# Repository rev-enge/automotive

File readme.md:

# Automotive electronics

Reverse engineered (parts) of electronic equipment from all kinds of
 automotive stuff like cars / diesel engines etc.

Probably most of it are only small reverse engineered parts, pinouts etc.

# Table of contents

* ECM2.1 => [Volvo/ECM2.1](Volvo/ecm2.1/readme.md)

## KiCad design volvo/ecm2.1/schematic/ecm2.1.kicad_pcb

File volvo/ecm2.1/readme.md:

# Identification of the module

Article numer: 60100001 P06

# Description

This unit is an ECM2.1 for a TAD734GE 6 Cylinder 250kW diesel Engine.

# Utilities used to create the drawings

The schematic diagram is made with KiCad 6.0.11

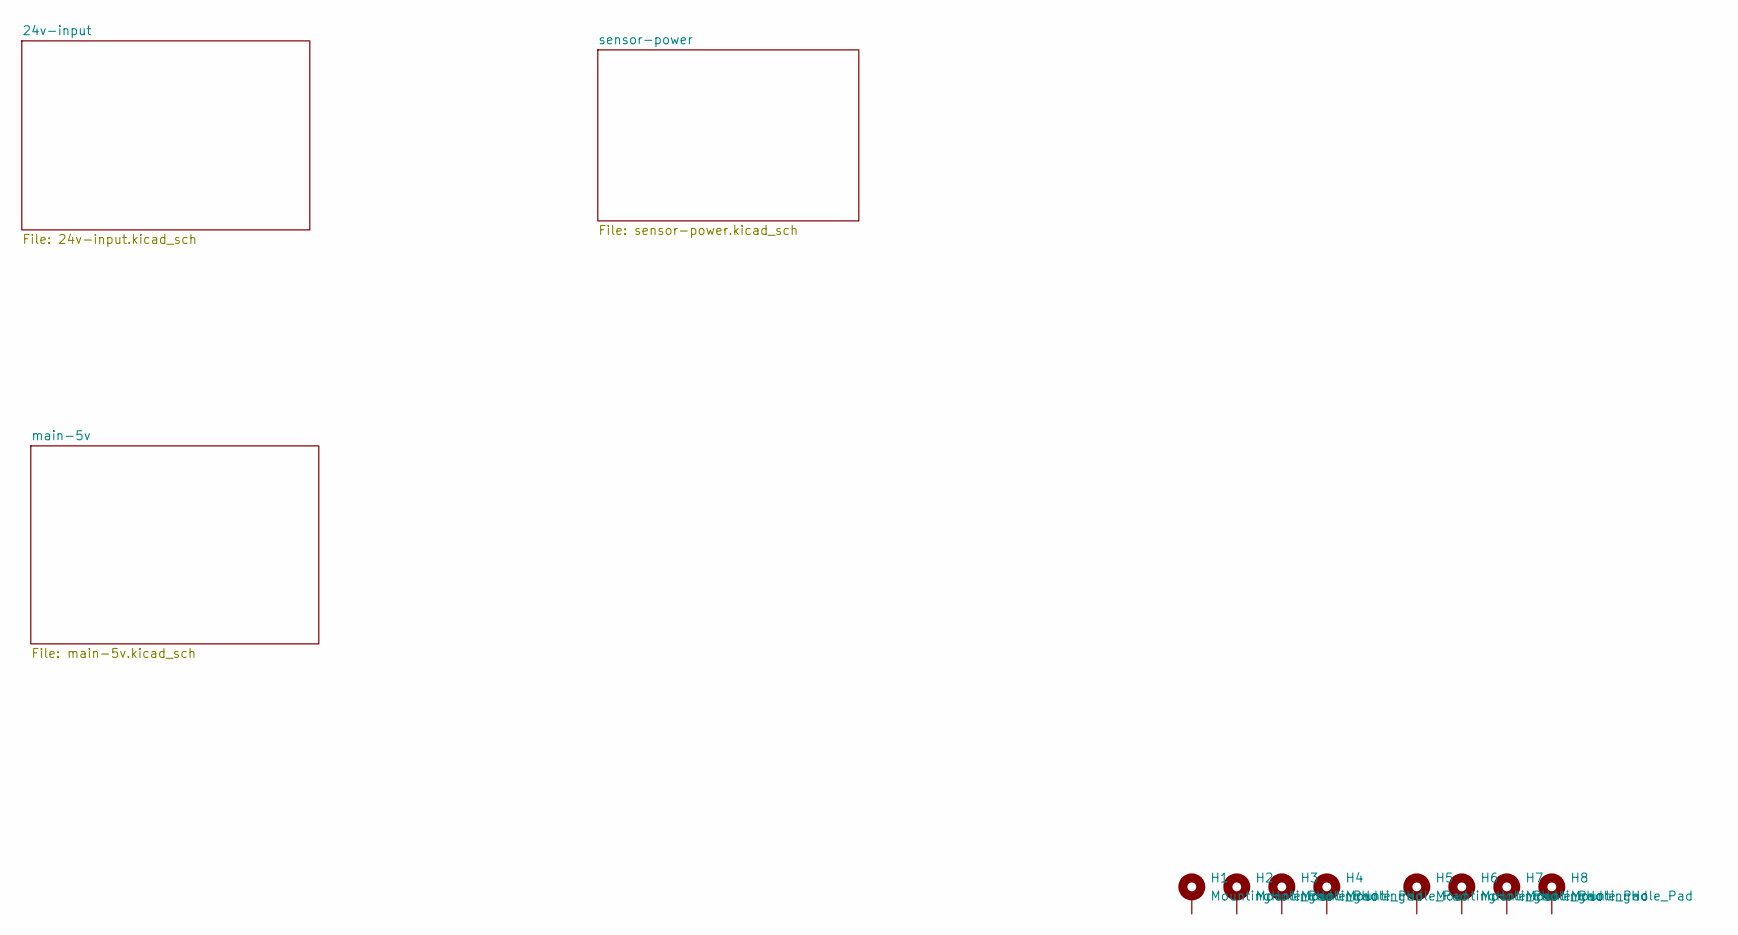
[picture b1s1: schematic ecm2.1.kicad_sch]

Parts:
H1, H2, H3, H4: MountingHole_Pad; MountingHole_5mm_Pad_Via
H5, H6, H7, H8: MountingHole_Pad; MountingHole_5.3mm_M5_DIN965_Pad_TopBottom

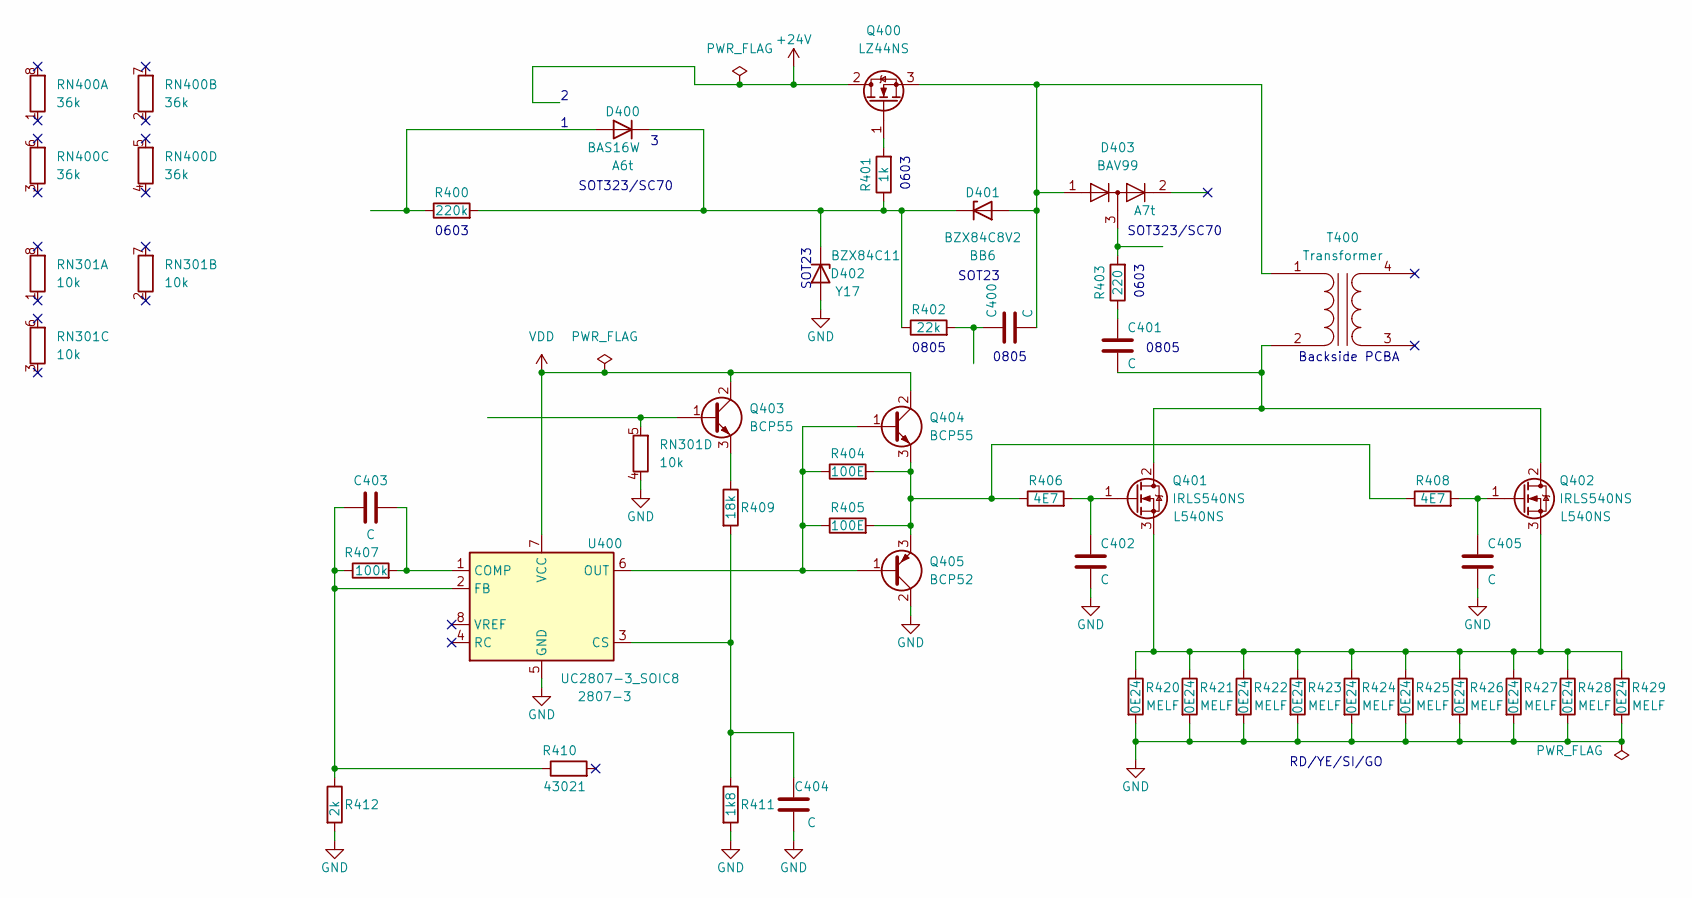
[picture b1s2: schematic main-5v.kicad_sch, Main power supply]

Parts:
C400, C401, C402, C403, C404, C405: C; C_0805_2012Metric
D400: BAS16W; SOT-323_SC-70
D401: BZX84C8V2; SOT-23
D402: BZX84C11; SOT-23
D403: BAV99; SOT-23
Q400: LZ44NS; TO-252-2
Q401, Q402: IRLS540NS; TO-252-3_TabPin2
Q403, Q404: BCP55; SOT-223
Q405: BCP52; SOT-223
R400: 220k; R_0603_1608Metric
R401: 1k; R_0603_1608Metric
R402: 22k; R_0805_2012Metric
R403: 220; R_0603_1608Metric
R404, R405: 100E; R_0805_2012Metric
R406, R408: 4E7; R_0805_2012Metric
R407: 100k; R_0805_2012Metric
R409: 18k; R_0805_2012Metric
R410: 43021; R_0805_2012Metric
R411: 1k8; R_0805_2012Metric
R412: 2k; R_0805_2012Metric
R420, R421, R422, R423, R424, R425, R426, R427, R428, R429: 0E24; R_1206_3216Metric
RN301: 10k; R_Array_Convex_4x0603
RN400: 36k; R_Array_Convex_4x0603
T400: Transformer; Transformer_37x44
U400: UC2807-3_SOIC8; SOIC-8_3.9x4.9mm_P1.27mm

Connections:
+24V: Q400.2 (D)
GND: C402.2, C404.1, C405.2, D402.1 (A), Q405.2 (C), Q405.4 (C), R411.2, R412.2, R420.2, R421.2, R422.2, R423.2, R424.2, R425.2, R426.2, R427.2, R428.2, R429.2, RN301.4 (R4.1), U400.5 (GND)
unnamed: C400.1, R402.2
unnamed: C400.2, D401.1 (A), D403.1 (K), Q400.3 (S), T400.1 (AA)
unnamed: C401.1, R403.1
unnamed: C401.2, Q401.2 (D), Q402.2 (D), T400.2 (AB)
unnamed: C402.1, Q401.1 (G), R406.2
unnamed: C403.1, R407.1, R410.1, R412.1, U400.2 (FB)
unnamed: C403.2, R407.2, U400.1 (COMP)
unnamed: C404.2, R409.2, R411.1, U400.3 (CS)
unnamed: C405.1, Q402.1 (G), R408.2
unnamed: D400.1 (A), R400.1
unnamed: D400.3 (K), D401.3 (K), D402.3 (K), R400.2, R401.1, R402.1
unnamed: D403.3 (K), R403.2
unnamed: Q400.1 (G), R401.2
unnamed: Q401.3 (S), Q402.3 (S), R420.1, R421.1, R422.1, R423.1, R424.1, R425.1, R426.1, R427.1, R428.1, R429.1
unnamed: Q403.1 (B), RN301.5 (R4.2)
unnamed: Q403.3 (E), R409.1
unnamed: Q404.1 (B), Q405.1 (B), R404.1, R405.1, U400.6 (OUT)
unnamed: Q404.3 (E), Q405.3 (E), R404.2, R405.2, R406.1, R408.1
VDD: Q403.2 (C), Q403.4 (C), Q404.2 (C), Q404.4 (C), U400.7 (VCC)

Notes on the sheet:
0603
SOT23
SOT323/SC70
0805
RD/YE/SI/GO
Backside PCBA

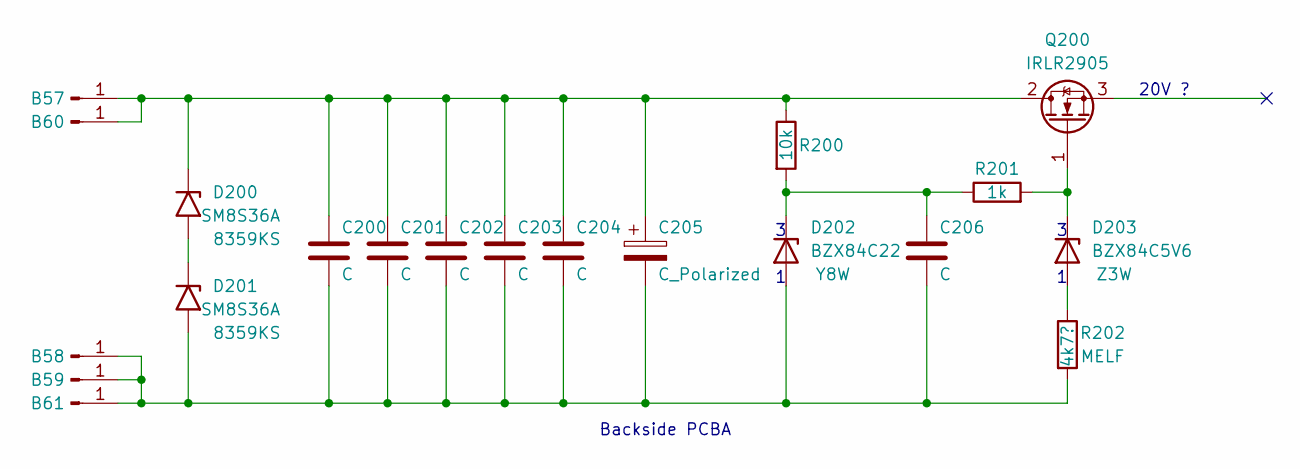
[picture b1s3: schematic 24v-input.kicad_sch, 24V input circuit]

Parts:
B57, B58, B59, B60, B61: Conn_01x01_Male; Pin_D1.4mm_L8.5mm_W2.8mm_FlatFork
C200, C201, C202, C203, C204: C; C_1210_3225Metric
C205: C_Polarized; CP_Radial_D12.5mm_P7.50mm
C206: C; C_0603_1608Metric
D200, D201: SM8S36A; D_DO-201AE_P15.24mm_Horizontal
D202: BZX84C22; SOT-23
D203: BZX84C5V6; SOT-23
Q200: IRLR2905; TO-252-2
R200: 10k; R_0603_1608Metric
R201: 1k; R_0603_1608Metric
R202: 4k7?; R_1206_3216Metric

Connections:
unnamed: B57.1, B60.1, C200.1, C201.1, C202.1, C203.1, C204.1, C205.1, D200.1 (A1), Q200.2 (D), R200.1
unnamed: B58.1, B59.1, B61.1, C200.2, C201.2, C202.2, C203.2, C204.2, C205.2, C206.2, D201.2 (A2), D202.1 (A), R202.2
unnamed: C206.1, D202.3 (K), R200.2, R201.1
unnamed: D200.2 (A2), D201.1 (A1)
unnamed: D203.1 (A), R202.1
unnamed: D203.3 (K), Q200.1 (G), R201.2

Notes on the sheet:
20V ?
Backside PCBA

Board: 2 copper layers, 71 parts (2 on the bottom side), 26 nets, no tracks yet.

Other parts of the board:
He: MountingHole_Pad; MountingHole_5mm_Pad_Via
